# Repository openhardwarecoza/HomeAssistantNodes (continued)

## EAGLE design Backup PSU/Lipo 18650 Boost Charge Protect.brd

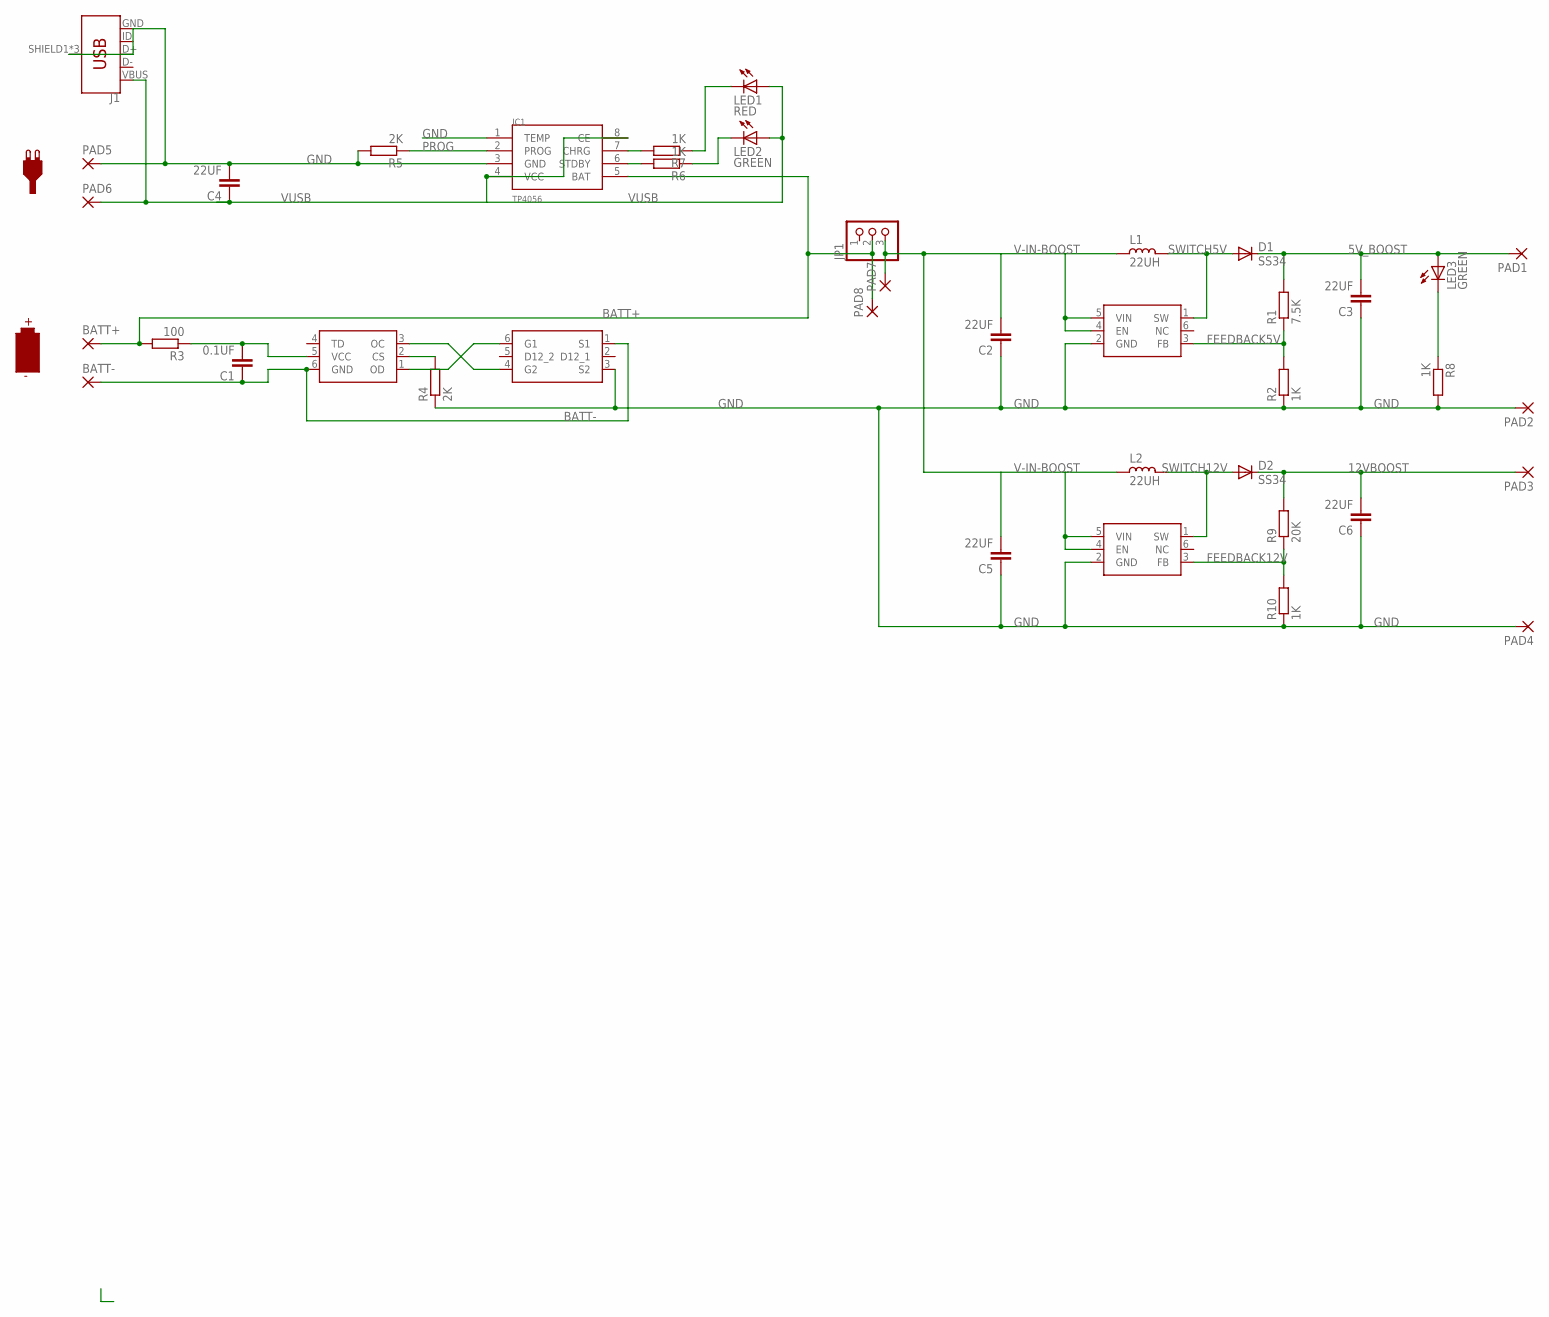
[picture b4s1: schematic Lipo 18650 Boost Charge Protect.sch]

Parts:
BATT+: 3,81/1,4
BATT-: 3,81/1,4
C1: 0.1UF; C1206@1
C2, C3, C4, C5, C6: 22UF; C1812K@1
D1, D2: SS34; DO-214AC
IC1: TP4056; SOP-8
J1: USB_MICRO-B_FEMALE-SMT; USB-B-MICRO-SMD
JP1: PINHD-1X3CB; 1X03-CLEANBIG
L1, L2: 22UH; CD75
LED1: RED; CHIPLED_0805
LED2, LED3: GREEN; CHIPLED_0805
PAD1, PAD2, PAD3, PAD4: SMD5; SMD2,54-5,08
PAD5, PAD6, PAD7, PAD8: SMD2; SMD1,27-2,54
R1: 7.5K; R1206
R2, R8, R10: 1K; R1206
R3: 100; R1206
R4, R5: 2K; R1206
R6, R7: 1K; R0603
R9: 20K; R1206
U$1: FS312F-G; SOT23-6
U$2: FS8205; SOT23-6
U$3, U$4: MT3608; SOT23-6

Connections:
5V_BOOST: C3.2, D1.1 (C), LED3.A, PAD1.1, R1.2
12VBOOST: C6.2, D2.1 (C), PAD3.1, R9.2
BATT+: BATT+.1, IC1.5 (BAT), JP1.2, PAD8.1, R3.2
BATT-: BATT-.1, C1.1, U$1.6 (GND), U$2.1 (S1)
CHG: IC1.7 (CHRG), R7.2
FEEDBACK5V: R1.1, R2.2, U$3.3 (FB)
FEEDBACK12V: R9.1, R10.2, U$4.3 (FB)
GND: C2.1, C3.1, C4.2, C5.1, C6.1, IC1.1 (TEMP), IC1.3 (GND), J1.GND, J1.SHIELD1 (SHIELD), J1.SHIELD2 (SHIELD), J1.SHIELD3 (SHIELD), PAD2.1, PAD4.1, PAD5.1, R2.1, R4.1, R5.2, R8.2, R10.1, U$2.3 (S2), U$3.2 (GND), U$4.2 (GND)
LEDCHR: LED1.C, R7.1
LEDSBY: LED2.C, R6.1
unnamed: R4.2, U$1.2 (CS)
unnamed: LED3.C, R8.1
OC: U$1.3 (OC), U$2.4 (G2)
OD: U$1.1 (OD), U$2.6 (G1)
PROG: IC1.2 (PROG), R5.1
STANDBY: IC1.6 (STDBY), R6.2
SWITCH5V: D1.2 (A), L1.1, U$3.1 (SW)
SWITCH12V: D2.2 (A), L2.1, U$4.1 (SW)
V-IN-BOOST: C2.2, C5.2, JP1.3, L1.2, L2.2, PAD7.1, U$3.4 (EN), U$3.5 (VIN), U$4.4 (EN), U$4.5 (VIN)
VCC-PROT: C1.2, R3.1, U$1.5 (VCC)
VUSB: C4.1, IC1.4 (VCC), IC1.8 (CE), J1.VBUS, LED1.A, LED2.A, PAD6.1

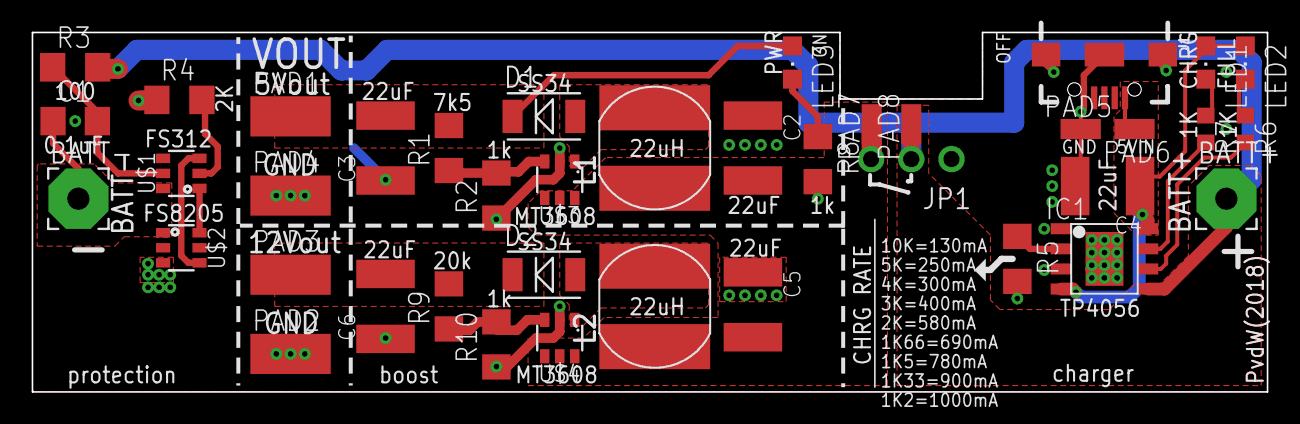
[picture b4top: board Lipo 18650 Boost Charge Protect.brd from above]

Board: 2 copper layers, 78.0 x 22.7 mm, 40 parts (0 on the bottom side), 21 nets.

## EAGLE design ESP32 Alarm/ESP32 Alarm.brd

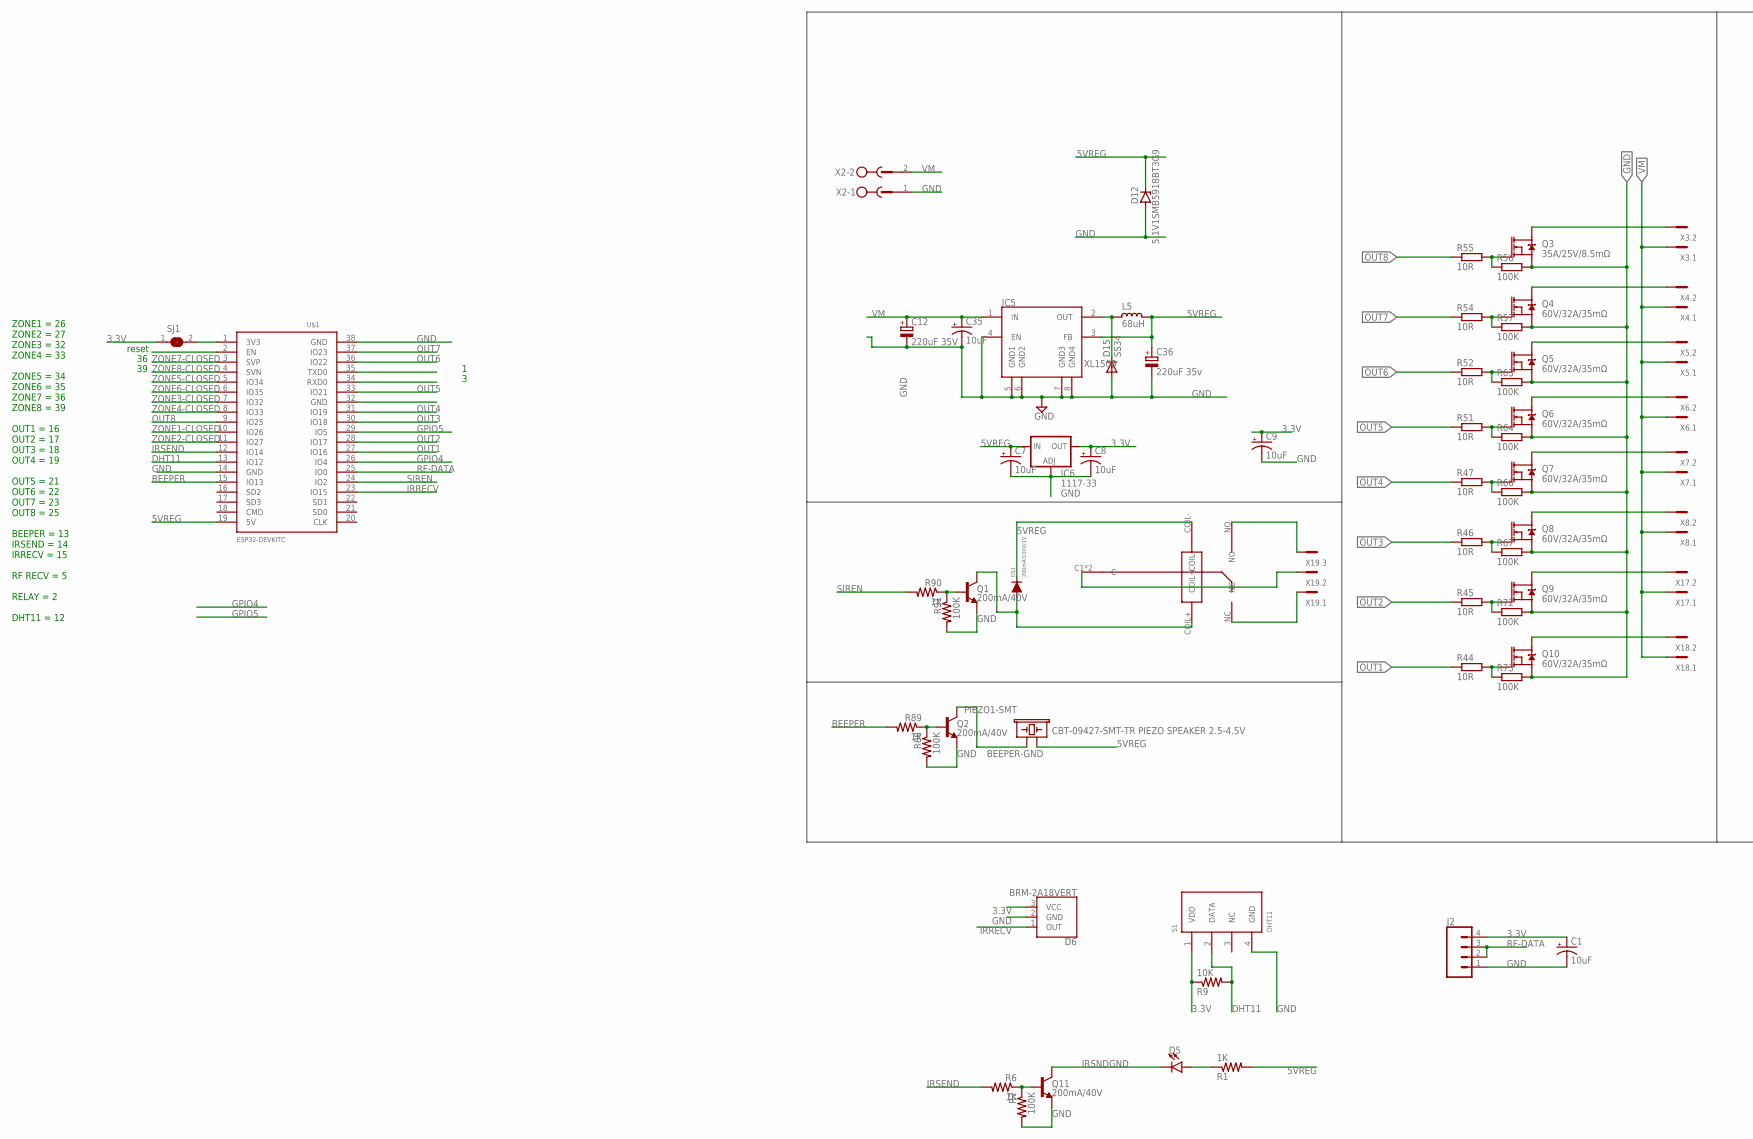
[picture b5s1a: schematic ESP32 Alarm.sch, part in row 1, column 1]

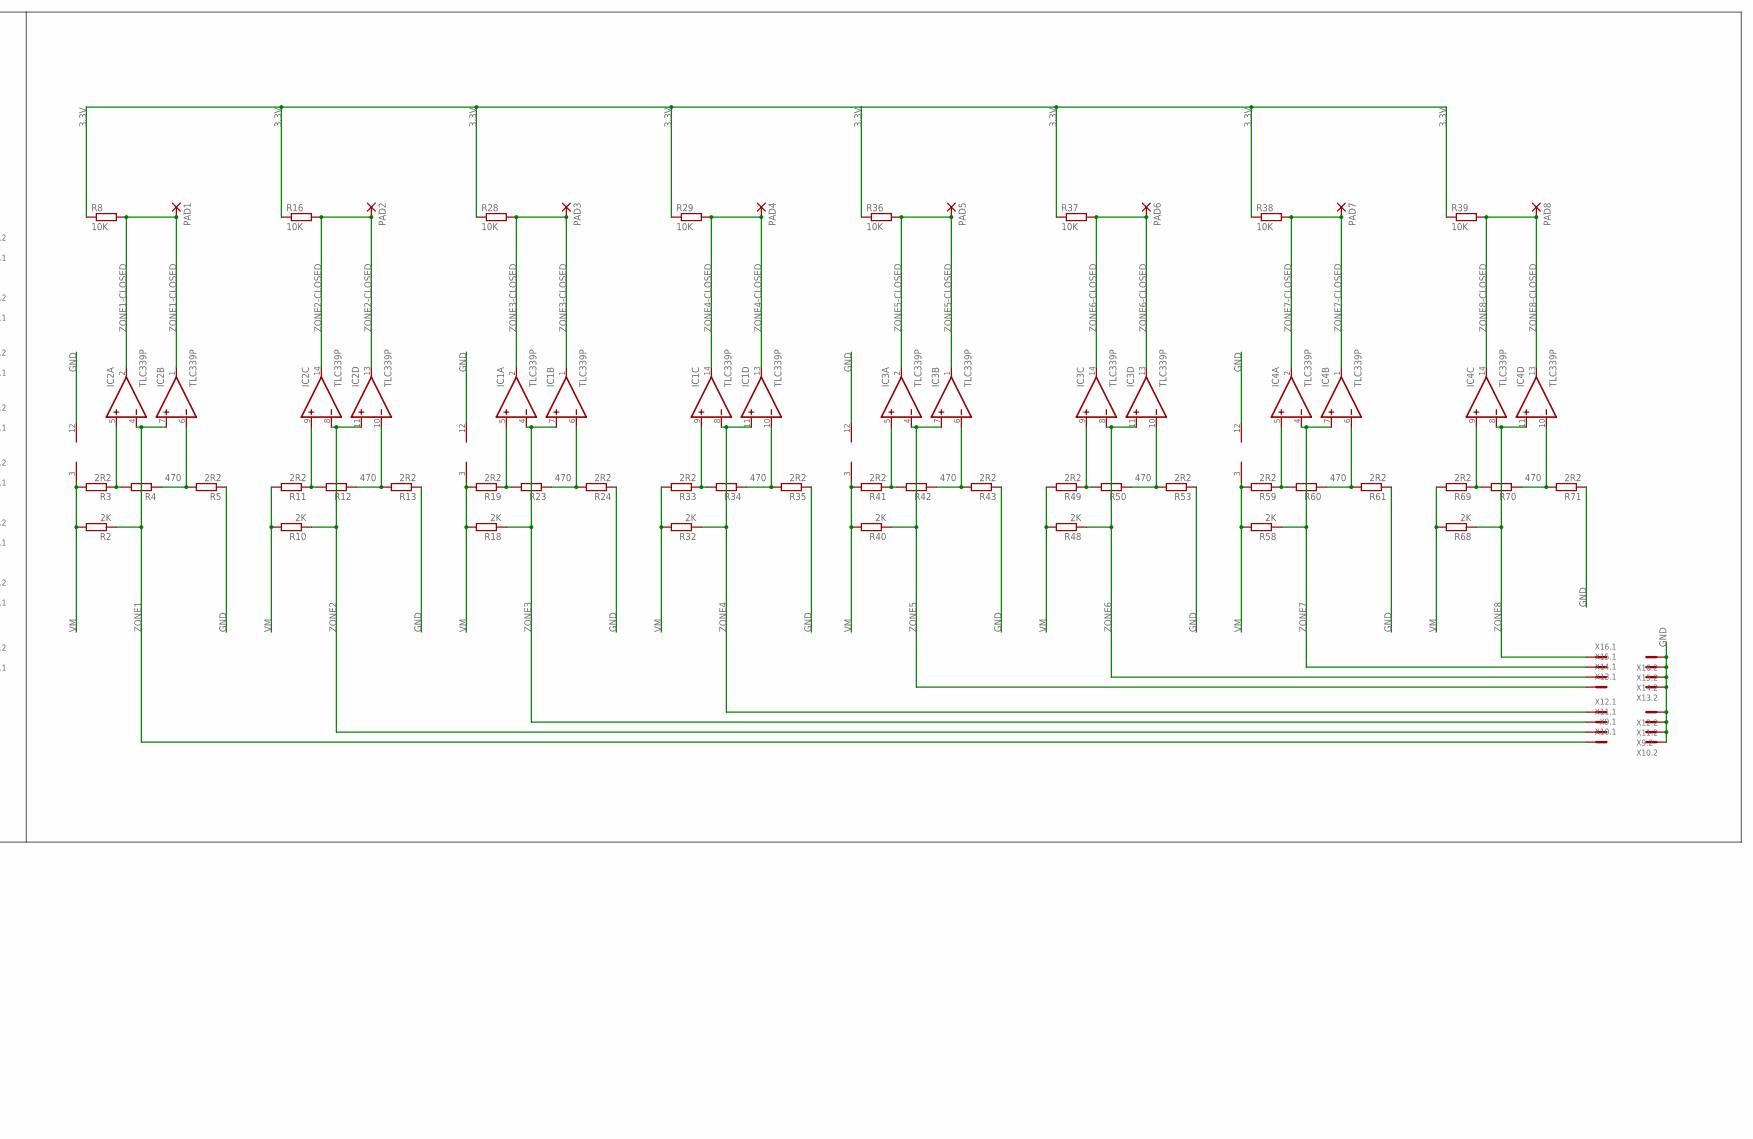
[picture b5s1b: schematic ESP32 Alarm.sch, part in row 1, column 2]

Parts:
C1, C7, C8, C9, C35: 10uF; EIA3216
C12: 220uF 35V; E3,5-8
C36: 220uF 35v; E3,5-8
D5: LED3MM; LED_3MM
D6: BRM-2A18VERT; BRM-2508_VERT
D12: 5.1V1SMB5918BT3G9; SMB
D15: SS34; DO-214AC
D51: 200mA/100V/1V; DIODE-1N4148-KIT
IC1, IC2, IC3, IC4: TLC339P; DIL14
IC5: XL1509; SO08
IC6: 1117-33; SOT223
J1: JRC-21F-4100
J2: CONN_04LOCK; 1X04_LOCK
L5: 68uH; CD75
PAD1, PAD2, PAD3, PAD4, PAD5, PAD6, PAD7, PAD8: 2,15/1,0
PIEZO1-SMT: CBT-09427-SMT-TR PIEZO SPEAKER 2.5-4.5V; BUZZER-12MM
Q1, Q2, Q11: 200mA/40V; TO-92
Q3: 35A/25V/8.5mΩ; DPAK
Q4, Q5, Q6, Q7, Q8, Q9, Q10: 60V/32A/35mΩ; TO220V
R1, R6, R89, R90: 1K; 0204/7
R2, R10, R18, R32, R40, R48, R58, R68: 2K; 0204/7
R3, R5, R11, R13, R19, R24, R33, R35, R41, R43, R49, R53, R59, R61, R69, R71: 2R2; 0204/7
R4, R12, R23, R34, R42, R50, R60, R70: 470; 0204/7
R7, R56, R57, R63, R64, R66, R67, R72, R73, R88, R91: 100K; 0204/7
R8, R9, R16, R28, R29, R36, R37, R38, R39: 10K; 0204/7
R44, R45, R46, R47, R51, R52, R54, R55: 10R; 0204/7
S1: DHT11
SJ1: SJ
U$1: ESP32DEVKITC; ESP32-DEVKITC
X2: MSTBV2
X3, X4, X5, X6, X7, X8, X9, X10, X11, X12, X13, X14, X15, X16, X17, X18: MCV2
X19: MCV3

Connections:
3.3V: C1.A (+), C8.A (+), C9.A (+), D6.3 (VCC), IC6.4 (OUT), J2.4, R8.1, R9.1, R16.1, R28.1, R29.1, R36.1, R37.1, R38.1, R39.1, S1.1 (VDD), SJ1.1
5VREG: C7.A (+), C36.+, D12.C, D51.C, IC5.3 (FB), IC6.3 (IN), J1.COIL-, L5.1, PIEZO1-SMT.+ (1), R1.2, U$1.19 (5V)
BEEPER: R89.2, U$1.15 (IO13)
BEEPER-GND: PIEZO1-SMT.- (2), Q2.3 (C)
COIL-1: D51.A, J1.COIL+ (COIL=), Q1.3 (C)
DHT11: R9.2, S1.2 (DATA), U$1.13 (IO12)
GND: C1.C (-), C7.C (-), C8.C (-), C9.C (-), C12.-, C35.C (-), C36.-, D6.2 (GND), D12.A, D15.2 (A), IC1.12 (V-), IC2.12 (V-), IC3.12 (V-), IC4.12 (V-), IC5.4 (EN), IC5.5 (GND1), IC5.6 (GND2), IC5.7 (GND3), IC5.8 (GND4), IC6.1 (ADJ), J2.1, Q1.1 (E), Q2.1 (E), Q3.3 (S), Q4.3 (S), Q5.3 (S), Q6.3 (S), Q7.3 (S), Q8.3 (S), Q9.3 (S), Q10.3 (S), Q11.1 (E), R5.1, R7.2, R13.1, R24.1, R35.1, R43.1, R53.1, R56.2, R57.2, R61.1, R63.2, R64.2, R66.2, R67.2, R71.1, R72.2, R73.2, R88.2, R91.2, S1.4 (GND), U$1.14 (GND), U$1.38 (GND), X2.1, X9.2, X10.2, X11.2, X12.2, X13.2, X14.2, X15.2, X16.2
GPIO4: U$1.26 (IO4)
GPIO5: U$1.29 (IO5)
IRRECV: D6.1 (OUT), U$1.23 (IO15)
IRSEND: R6.2, U$1.12 (IO14)
IRSNDGND: D5.K (C), Q11.3 (C)
unnamed: J1.C1 (C), J1.C2 (C), X19.2
unnamed: IC2.5 (+IN), R3.1, R4.2
unnamed: D15.1 (C), IC5.2 (OUT), L5.2
unnamed: IC2.6 (-IN), R4.1, R5.2
unnamed: IC1.5 (+IN), R19.1, R23.2
unnamed: IC1.6 (-IN), R23.1, R24.2
unnamed: Q9.2 (D), X17.2
unnamed: D5.A, R1.1
unnamed: Q11.2 (B), R6.1, R7.1
unnamed: Q2.2 (B), R88.1, R89.1
unnamed: IC2.9 (+IN), R11.1, R12.2
unnamed: IC2.10 (-IN), R12.1, R13.2
unnamed: Q10.1 (G), R44.2, R73.1
unnamed: J1.NC, X19.1
unnamed: Q9.1 (G), R45.2, R72.1
unnamed: Q8.1 (G), R46.2, R67.1
unnamed: IC1.9 (+IN), R33.1, R34.2
unnamed: IC1.10 (-IN), R34.1, R35.2
unnamed: Q7.1 (G), R47.2, R66.1
unnamed: IC3.5 (+IN), R41.1, R42.2
unnamed: IC3.6 (-IN), R42.1, R43.2
unnamed: J1.NO, X19.3
unnamed: Q6.1 (G), R51.2, R64.1
unnamed: IC3.9 (+IN), R49.1, R50.2
unnamed: IC3.10 (-IN), R50.1, R53.2
unnamed: SJ1.2, U$1.1 (3V3)
unnamed: Q5.1 (G), R52.2, R63.1
unnamed: IC4.5 (+IN), R59.1, R60.2
unnamed: IC4.6 (-IN), R60.1, R61.2
unnamed: Q4.1 (G), R54.2, R57.1
unnamed: IC4.9 (+IN), R69.1, R70.2
unnamed: Q3.1 (G), R55.2, R56.1
unnamed: IC4.10 (-IN), R70.1, R71.2
unnamed: Q3.4 (D), X3.2
unnamed: Q4.2 (D), X4.2
unnamed: Q5.2 (D), X5.2
unnamed: Q6.2 (D), X6.2
unnamed: Q7.2 (D), X7.2
unnamed: Q10.2 (D), X18.2
unnamed: Q8.2 (D), X8.2
unnamed: Q1.2 (B), R90.1, R91.1
OUT1: R44.1, U$1.27 (IO16)
OUT2: R45.1, U$1.28 (IO17)
OUT3: R46.1, U$1.30 (IO18)
OUT4: R47.1, U$1.31 (IO19)
OUT5: R51.1, U$1.33 (IO21)
OUT6: R52.1, U$1.36 (IO22)
OUT7: R54.1, U$1.37 (IO23)
OUT8: R55.1, U$1.9 (IO25)
RF-DATA: J2.2, J2.3, U$1.25 (IO0)
SIREN: R90.2, U$1.24 (IO2)
VM: C12.+, C35.A (+), IC1.3 (V+), IC2.3 (V+), IC3.3 (V+), IC4.3 (V+), IC5.1 (IN), R2.2, R3.2, R10.2, R11.2, R18.2, R19.2, R32.2, R33.2, R40.2, R41.2, R48.2, R49.2, R58.2, R59.2, R68.2, R69.2, X2.2, X3.1, X4.1, X5.1, X6.1, X7.1, X8.1, X17.1, X18.1
ZONE1: IC2.4 (-IN), IC2.7 (+IN), R2.1, X10.1
ZONE1-CLOSED: IC2.1 (OUT), IC2.2 (OUT), PAD1.1, R8.2, U$1.10 (IO26)
ZONE2: IC2.8 (-IN), IC2.11 (+IN), R10.1, X9.1
ZONE2-CLOSED: IC2.13 (OUT), IC2.14 (OUT), PAD2.1, R16.2, U$1.11 (IO27)
ZONE3: IC1.4 (-IN), IC1.7 (+IN), R18.1, X11.1
ZONE3-CLOSED: IC1.1 (OUT), IC1.2 (OUT), PAD3.1, R28.2, U$1.7 (IO32)
ZONE4: IC1.8 (-IN), IC1.11 (+IN), R32.1, X12.1
ZONE4-CLOSED: IC1.13 (OUT), IC1.14 (OUT), PAD4.1, R29.2, U$1.8 (IO33)
ZONE5: IC3.4 (-IN), IC3.7 (+IN), R40.1, X13.1
ZONE5-CLOSED: IC3.1 (OUT), IC3.2 (OUT), PAD5.1, R36.2, U$1.5 (IO34)
ZONE6: IC3.8 (-IN), IC3.11 (+IN), R48.1, X14.1
ZONE6-CLOSED: IC3.13 (OUT), IC3.14 (OUT), PAD6.1, R37.2, U$1.6 (IO35)
ZONE7: IC4.4 (-IN), IC4.7 (+IN), R58.1, X15.1
ZONE7-CLOSED: IC4.1 (OUT), IC4.2 (OUT), PAD7.1, R38.2, U$1.3 (SVP)
ZONE8: IC4.8 (-IN), IC4.11 (+IN), R68.1, X16.1
ZONE8-CLOSED: IC4.13 (OUT), IC4.14 (OUT), PAD8.1, R39.2, U$1.4 (SVN)

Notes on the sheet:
reset
ZONE1 = 26 ZONE2 = 27 ZONE3 = 32 ZONE4 = 33 ZONE5 = 34 ZONE6 = 35 ZONE7 = 36 ZONE8 = 39 OUT1 = 16 OUT2 = 17 OUT3 = 18 OUT4 = 19 OUT5 = 21 OUT6 = 22 OUT7 = 23 OUT8 = 25 BEEPER = 13 IRSEND = 14 IRRECV = 15 RF RECV = 5 RELAY = 2 DHT11 = 12

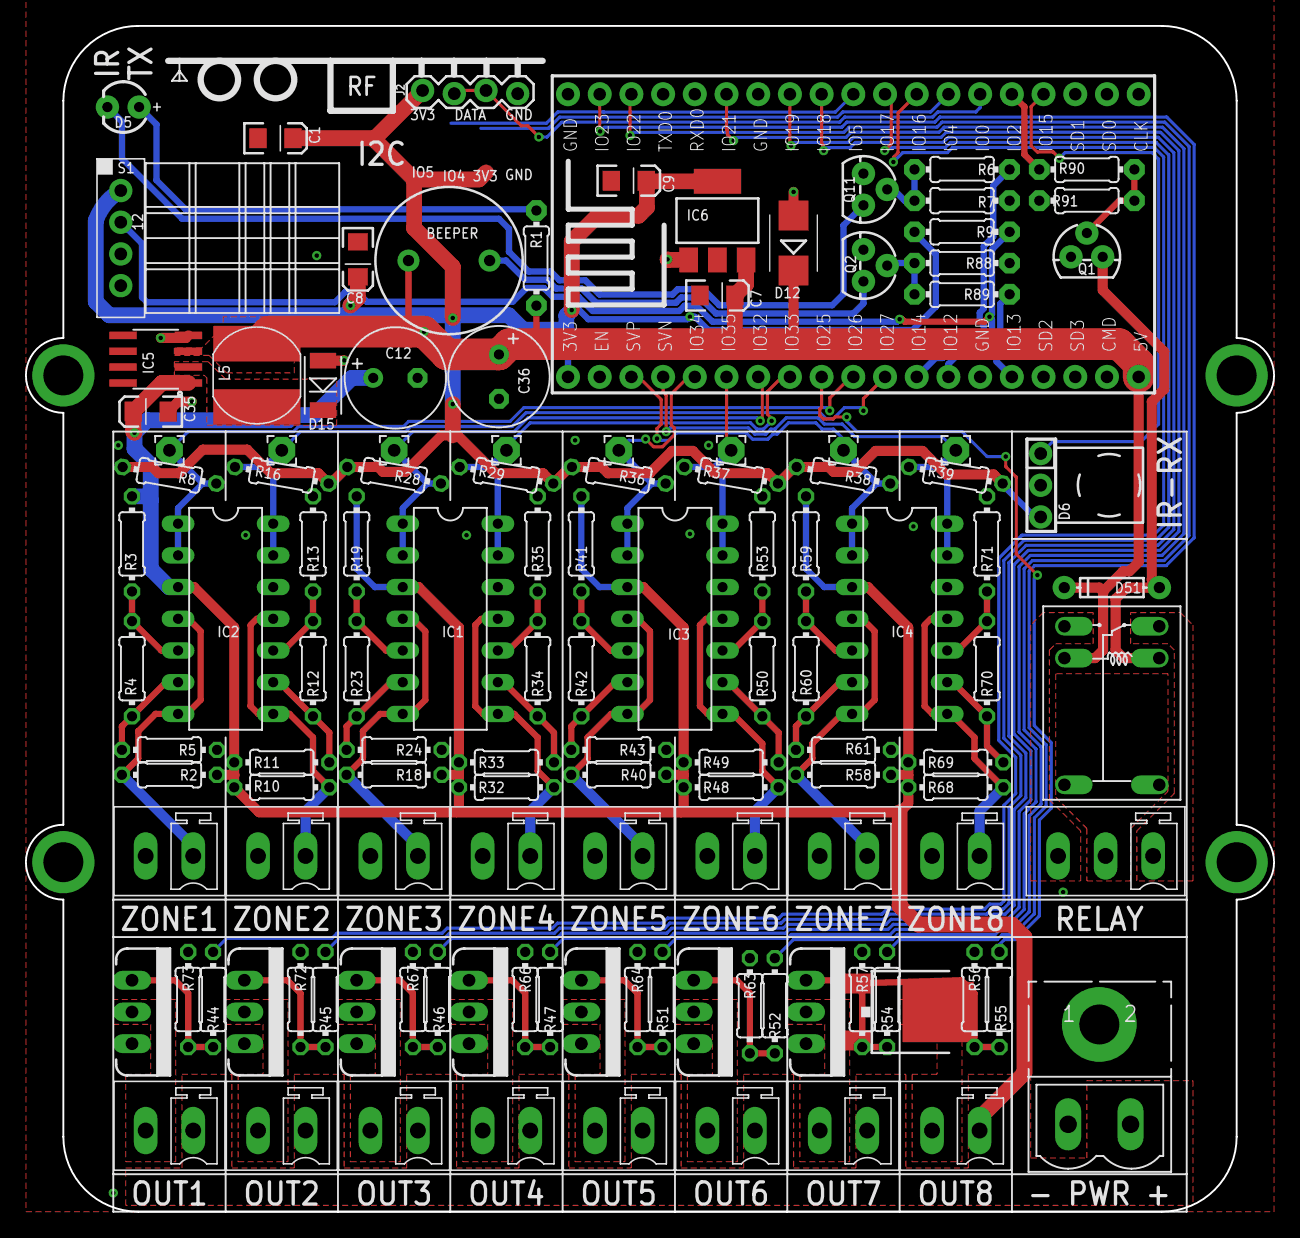
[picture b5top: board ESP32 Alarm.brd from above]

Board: 2 copper layers, 100.0 x 95.0 mm, 126 parts (1 on the bottom side), 78 nets.

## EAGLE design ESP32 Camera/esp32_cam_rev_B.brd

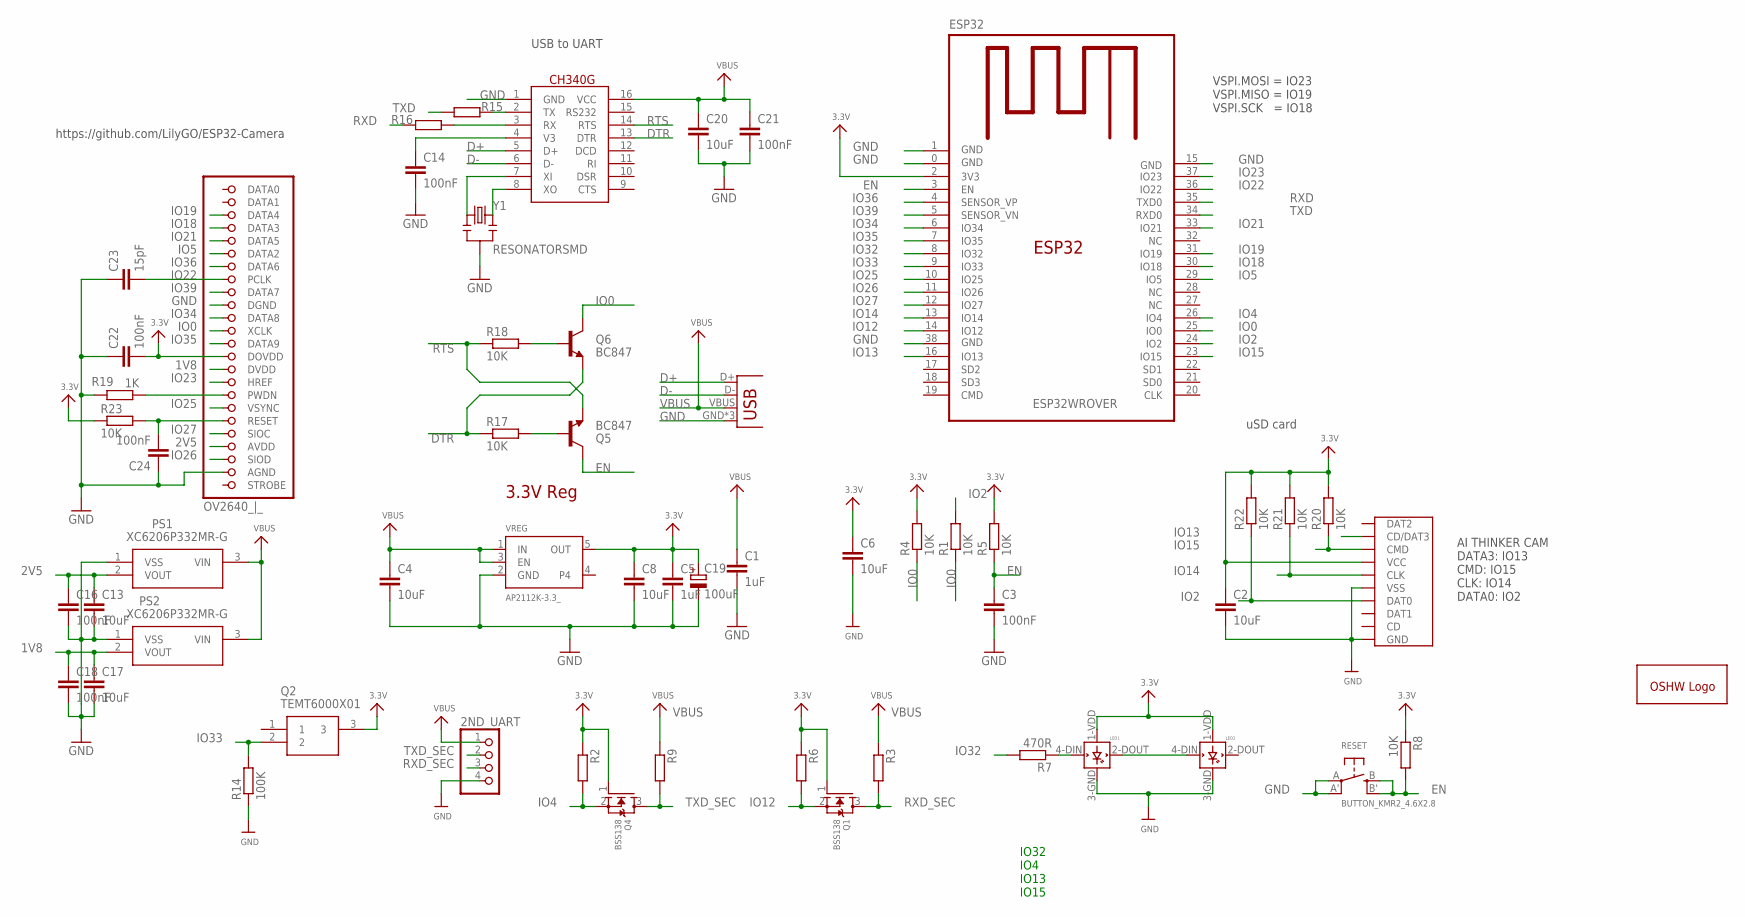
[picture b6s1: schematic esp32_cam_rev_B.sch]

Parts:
2ND_UART: JST_PH4; JSTPH4
C1: 1uF; C0805K
C2, C4, C8, C13, C17, C20: 10uF; C0805
C3, C14: 100nF; C0805K
C5: 1uF; C0805
C6: 10uF; C0805K
C16, C18, C21, C22, C24: 100nF; C0805
C19: 100uF; CT6032
C23: 15pF; C0805
CH340G: CH340G; SO16
ESP32: ESP32WROVER
FPC_CONNECTOR: OV2640_|_; 5051102491
GOLD_ORB_SM1: OSHWLOGO_; OSHW_5MM_LOGO
LED1, LED2: WS2812B; WS2812B_5050
PS1, PS2: XC6206P332MR-G; SOT95P280X130-3N
Q1, Q4: BSS138; SOT95P240X110-3
Q2: TEMT6000X01
Q5, Q6: BC847; SOT23-3
R1, R2, R3, R4, R5, R6, R8, R9, R17, R18, R20, R21, R22, R23: 10K; R0805
R7, R15, R16: 470R; R0805
R14: 100K; R0805
R19: 1K; R0805
RESET: BUTTON_KMR2_4.6X2.8
SD_CARD: MICRO_SD_CARD_; TFP09-2--12B
USB: USB_MICRO_ATTEND_; USB_MICRO
VREG: AP2112K-3.3_; SOT95P290X120-5
Y1: RESONATORSMD; RESONATOR-SMD

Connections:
1V8: C17.1, C18.1, FPC_CONNECTOR.15 (DVDD), PS2.2 (VOUT)
2V5: C13.1, C16.1, FPC_CONNECTOR.21 (AVDD), PS1.2 (VOUT)
3.3V: C2.1, C5.1, C6.1, C8.1, C19.+, C22.2, ESP32.2 (3V3), FPC_CONNECTOR.14 (DOVDD), LED1.1-VDD (VDD), LED2.1-VDD (VDD), Q1.1 (G), Q2.3, Q4.1 (G), R2.1, R4.2, R5.2, R6.1, R8.1, R20.2, R21.2, R22.2, R23.1, SD_CARD.VCC, VREG.5 (OUT)
D+: CH340G.5 (D+), USB.D+
D-: CH340G.6 (D-), USB.D-
DTR: CH340G.13 (DTR), Q6.2 (E), R17.1
EN: C3.1, ESP32.3 (EN), Q5.3 (C), R5.1, R8.2, RESET.B (S), RESET.B' (S1)
GND: 2ND_UART.4, C1.2, C2.2, C3.2, C4.2, C5.2, C6.2, C8.2, C13.2, C14.2, C16.2, C17.2, C18.2, C19.-, C20.2, C21.2, C22.1, C23.1, C24.1, CH340G.1 (GND), ESP32.0 (GND), ESP32.1 (GND), ESP32.15 (GND), ESP32.38 (GND), FPC_CONNECTOR.10 (DGND), FPC_CONNECTOR.23 (AGND), LED1.3-GND (GND), LED2.3-GND (GND), PS1.1 (VSS), PS2.1 (VSS), R14.1, R19.2, RESET.A, RESET.A' (P1), SD_CARD.GND, SD_CARD.GND@1 (GND), SD_CARD.GND@2 (GND), SD_CARD.GND@3 (VSS), SD_CARD.VSS (GND), USB.GND, USB.GND@2 (GND), USB.GND@3 (GND), VREG.2 (GND), Y1.2
IO0: ESP32.25 (IO0), FPC_CONNECTOR.12 (XCLK), Q6.3 (C), R1.1, R4.1
IO2: ESP32.24 (IO2), R1.2, R22.1, SD_CARD.DAT0
IO4: ESP32.26 (IO4), Q4.2 (S), R2.2
IO5: ESP32.29 (IO5), FPC_CONNECTOR.6 (DATA2)
IO12: ESP32.14 (IO12), Q1.2 (S), R6.2
IO13: ESP32.16 (IO13), SD_CARD.CD/DAT3
IO14: ESP32.13 (IO14), R21.1, SD_CARD.CLK
IO15: ESP32.23 (IO15), R20.1, SD_CARD.CMD
IO18: ESP32.30 (IO18), FPC_CONNECTOR.4 (DATA3)
IO19: ESP32.31 (IO19), FPC_CONNECTOR.3 (DATA4)
IO21: ESP32.33 (IO21), FPC_CONNECTOR.5 (DATA5)
IO22: C23.2, ESP32.36 (IO22), FPC_CONNECTOR.8 (PCLK)
IO23: ESP32.37 (IO23), FPC_CONNECTOR.16 (HREF)
IO25: ESP32.10 (IO25), FPC_CONNECTOR.18 (VSYNC)
IO26: ESP32.11 (IO26), FPC_CONNECTOR.22 (SIOD)
IO27: ESP32.12 (IO27), FPC_CONNECTOR.20 (SIOC)
IO32: ESP32.8 (IO32), R7.2
IO33: ESP32.9 (IO33), Q2.2, R14.2
IO34: ESP32.6 (IO34), FPC_CONNECTOR.11 (DATA8)
IO35: ESP32.7 (IO35), FPC_CONNECTOR.13 (DATA9)
IO36: ESP32.4 (SENSOR_VP), FPC_CONNECTOR.7 (DATA6)
IO39: ESP32.5 (SENSOR_VN), FPC_CONNECTOR.9 (DATA7)
unnamed: LED1.4-DIN (DIN), R7.1
unnamed: LED1.2-DOUT (DOUT), LED2.4-DIN (DIN)
unnamed: CH340G.8 (XO), Y1.3
unnamed: CH340G.7 (XI), Y1.1
unnamed: C14.1, CH340G.4 (V3)
unnamed: CH340G.2 (TX), R15.1
unnamed: CH340G.3 (RX), R16.1
unnamed: Q5.1 (B), R17.2
unnamed: Q6.1 (B), R18.2
unnamed: FPC_CONNECTOR.17 (PWDN), R19.1
unnamed: C24.2, FPC_CONNECTOR.19 (RESET), R23.2
RTS: CH340G.14 (RTS), Q5.2 (E), R18.1
RXD: ESP32.35 (TXD0), R16.2
RXD_SEC: 2ND_UART.3, Q1.3 (D), R3.2
TXD: ESP32.34 (RXD0), R15.2
TXD_SEC: 2ND_UART.2, Q4.3 (D), R9.2
VBUS: 2ND_UART.1, C1.1, C4.1, C20.1, C21.1, CH340G.16 (VCC), PS1.3 (VIN), PS2.3 (VIN), R3.1, R9.1, USB.VBUS, VREG.1 (IN), VREG.3 (EN)

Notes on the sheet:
USB to UART
VSPI.MOSI = IO23 VSPI.MISO = IO19 VSPI.SCK = IO18
3.3V Reg
uSD card
https://github.com/LilyGO/ESP32-Camera
AI THINKER CAM DATA3: IO13 CMD: IO15 CLK: IO14 DATA0: IO2
IO32 IO4 IO13 IO15

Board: 2 copper layers, 56 parts (3 on the bottom side), 47 nets, no tracks yet.

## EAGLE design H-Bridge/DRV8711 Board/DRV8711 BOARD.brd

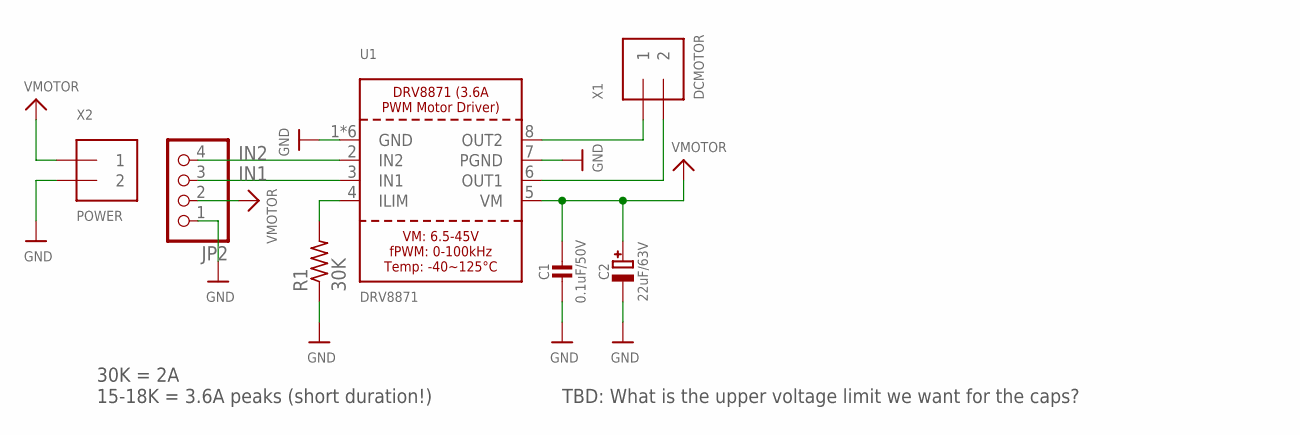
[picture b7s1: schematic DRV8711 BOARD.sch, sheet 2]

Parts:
C1: 0.1uF/50V; 0805-NO
C2: 22uF/63V; CELEC_3.5MM_10MM
JP2: HEADER-1X476MIL; 1X04_ROUND_76
R1: 30K; 0805-THM
U1: DRV8871; HSOP8
X1: DCMOTOR; TERMBLOCK_1X2-3.5MM
X2: POWER; TERMBLOCK_1X2-3.5MM

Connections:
GND: C1.2, C2.-, JP2.1, R1.1, U1.1 (GND), U1.7 (PGND), U1.GND, U1.P$1 (GND), U1.P$2 (GND), U1.P$3 (GND), U1.P$4 (GND), X2.2
IN1: JP2.3, U1.3 (IN1)
IN2: JP2.4, U1.2 (IN2)
unnamed: R1.2, U1.4 (ILIM)
OUT1: U1.6 (OUT1), X1.2
OUT2: U1.8 (OUT2), X1.1
VMOTOR: C1.1, C2.+, JP2.2, U1.5 (VM), X2.1

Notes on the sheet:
TBD: What is the upper voltage limit we want for the caps?
30K = 2A 15-18K = 3.6A peaks (short duration!)

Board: 2 copper layers, 7 parts (1 on the bottom side), 7 nets, no tracks yet.
